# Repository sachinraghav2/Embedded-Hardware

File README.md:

# Embedded-Hardware
Contains eagle file while I developed the PCB of a multibot.

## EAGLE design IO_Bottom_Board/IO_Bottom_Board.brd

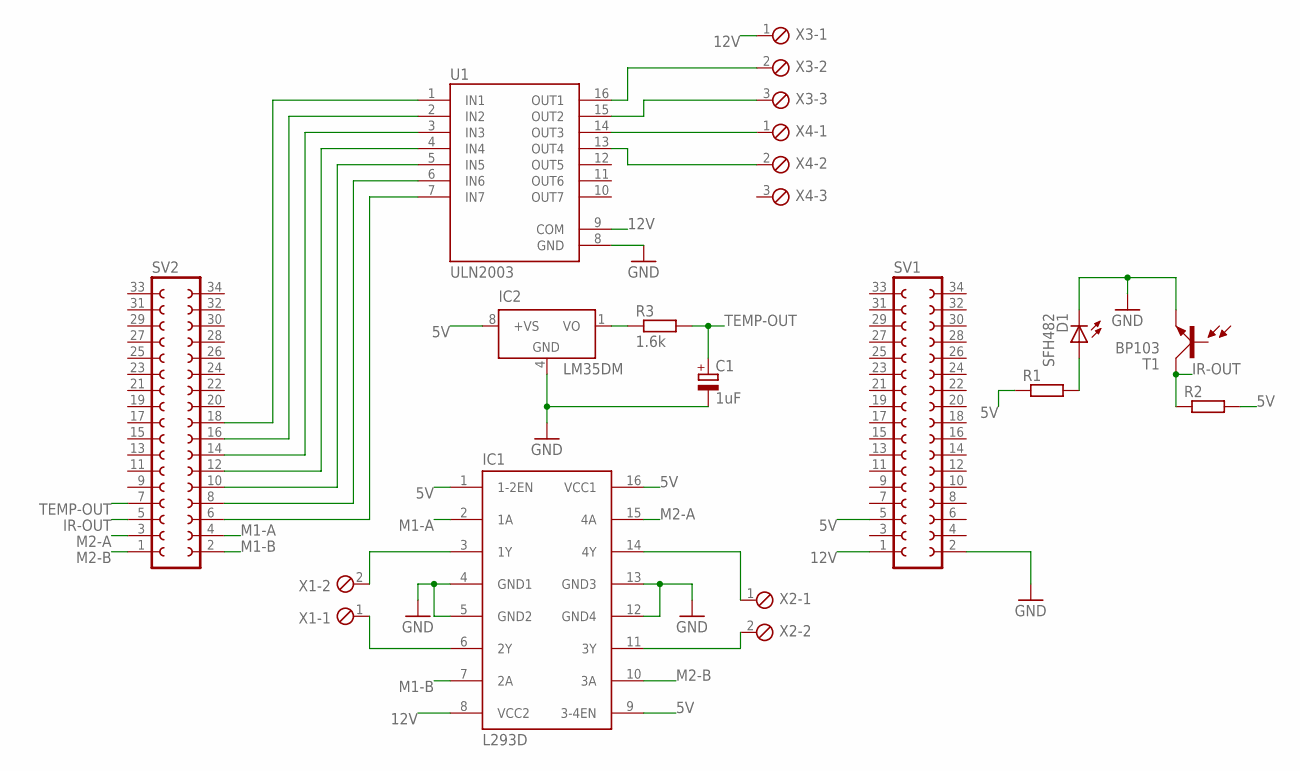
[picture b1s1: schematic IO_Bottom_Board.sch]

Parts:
C1: 1uF; CT3528
D1: SFH482
IC1: L293D; DIL16
IC2: LM35DM; SO08
R1, R2: R-EU_M2012; M2012
R3: 1.6k; M2012
SV1, SV2: FE17-2W
T1: BP103
U1: ULN2003; DIP762W46P254L1969H533Q16
X1, X2: MPT2; 2POL254
X3, X4: MPT3; 3POL254

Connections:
5V: IC1.1 (1-2EN), IC1.9 (3-4EN), IC1.16 (VCC1), IC2.8 (+VS), R1.1, R2.2, SV1.5
12V: IC1.8 (VCC2), SV1.1, U1.9 (COM), X3.1
GND: C1.-, D1.K (C), IC1.4 (GND1), IC1.5 (GND2), IC1.12 (GND4), IC1.13 (GND3), IC2.4 (GND), SV1.2, T1.E, U1.8 (GND)
IR-OUT: R2.1, SV2.5, T1.C
LM-OUT: IC2.1 (VO), R3.1
M1-A: IC1.2 (1A), SV2.4
M1-B: IC1.7 (2A), SV2.2
M2-A: IC1.15 (4A), SV2.3
M2-B: IC1.10 (3A), SV2.1
unnamed: IC1.3 (1Y), X1.2
unnamed: IC1.6 (2Y), X1.1
unnamed: IC1.14 (4Y), X2.1
unnamed: IC1.11 (3Y), X2.2
unnamed: SV2.6, U1.7 (IN7)
unnamed: SV2.8, U1.6 (IN6)
unnamed: SV2.10, U1.5 (IN5)
unnamed: SV2.12, U1.4 (IN4)
unnamed: SV2.14, U1.3 (IN3)
unnamed: SV2.16, U1.2 (IN2)
unnamed: SV2.18, U1.1 (IN1)
unnamed: U1.16 (OUT1), X3.2
unnamed: U1.15 (OUT2), X3.3
unnamed: U1.14 (OUT3), X4.1
unnamed: U1.13 (OUT4), X4.2
unnamed: D1.A, R1.2
TEMP-OUT: C1.+, R3.2, SV2.7

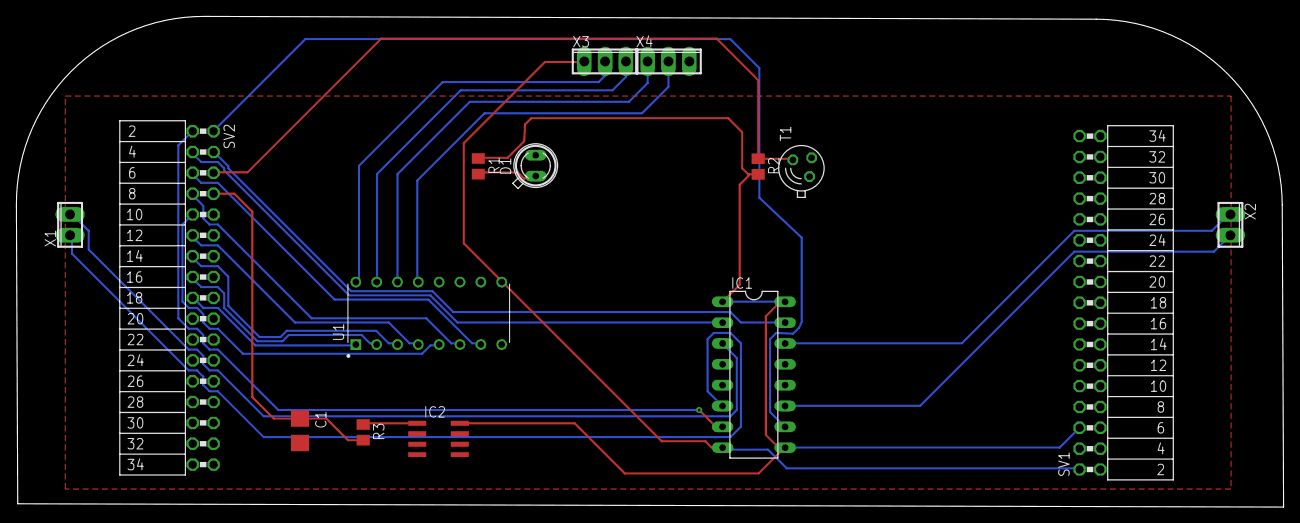
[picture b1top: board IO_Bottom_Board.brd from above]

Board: 2 copper layers, 154.5 x 59.8 mm, 15 parts (0 on the bottom side), 26 nets.

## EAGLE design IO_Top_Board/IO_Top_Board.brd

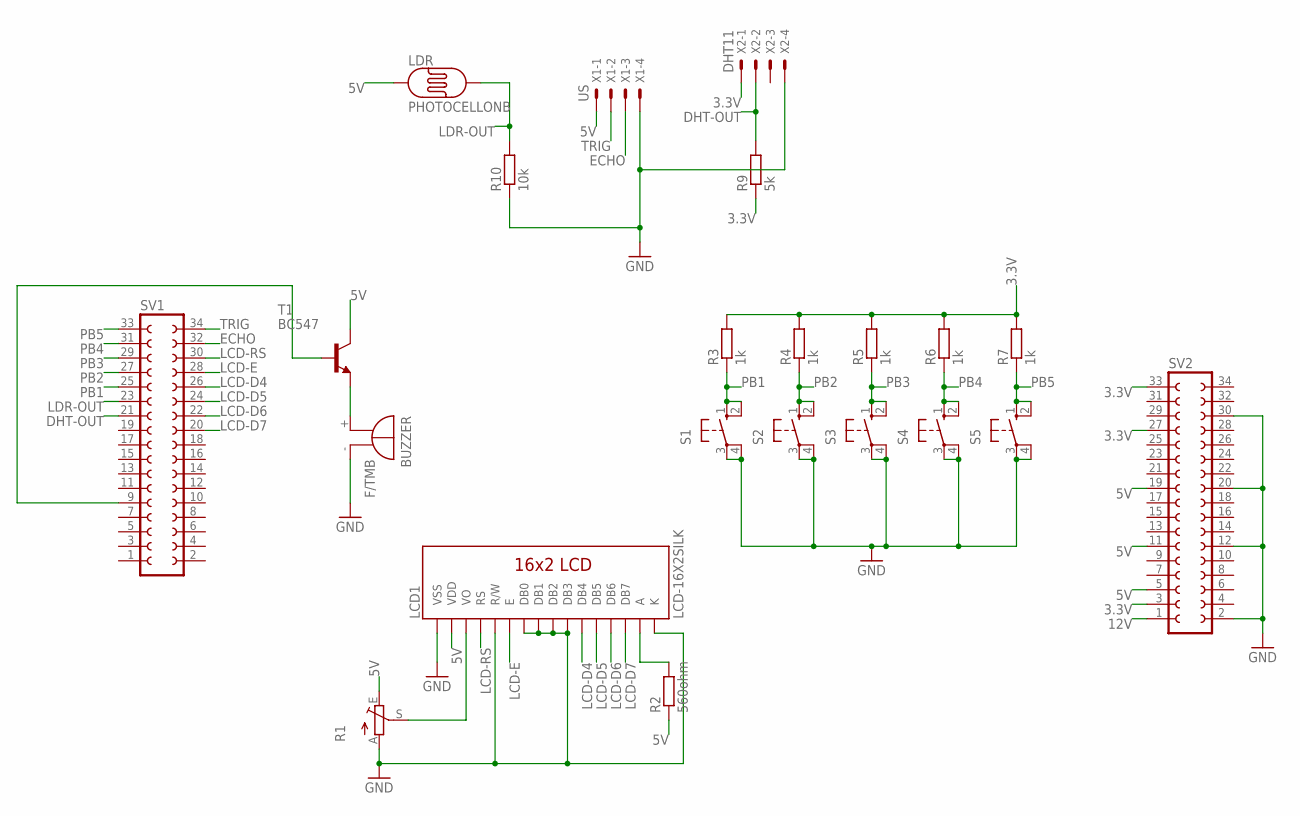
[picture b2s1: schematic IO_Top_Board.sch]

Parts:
BUZZER: F/TMB
LCD1: LCD-16X2SILK; LCD-16X2
LDR: PHOTOCELLONB; ON_BOARD
R1: TRIM_EU-CA6V; CA6V
R2: 560ohm; M0805
R3, R4, R5, R6, R7: 1k; M0805
R9: 5k; M0805
R10: 10k; M0805
S1, S2, S3, S4, S5: 10-XX; B3F-10XX
SV1, SV2: FE17-2W
T1: BC547; TO92
X1: US; 22-23-2041
X2: DHT11; 22-23-2041

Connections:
3.3V: R3.2, R4.2, R5.2, R6.2, R7.2, R9.1, SV2.3, SV2.27, SV2.33, X2.1
5V: LCD1.2 (VDD), LDR.1, R1.E, R2.1, SV2.5, SV2.11, SV2.19, T1.3 (C), X1.1
12V: SV2.1
DHT-OUT: R9.2, SV1.21, X2.2
ECHO: SV1.32, X1.3
GND: BUZZER.-, LCD1.1 (VSS), LCD1.5 (R/W), LCD1.7 (DB0), LCD1.8 (DB1), LCD1.9 (DB2), LCD1.10 (DB3), LCD1.16 (K), R1.A, R10.1, S1.3, S1.4 (P1), S2.3, S2.4 (P1), S3.3, S3.4 (P1), S4.3, S4.4 (P1), S5.3, S5.4 (P1), SV2.2, SV2.12, SV2.20, SV2.30, X1.4, X2.4
LCD-D4: LCD1.11 (DB4), SV1.26
LCD-D5: LCD1.12 (DB5), SV1.24
LCD-D6: LCD1.13 (DB6), SV1.22
LCD-D7: LCD1.14 (DB7), SV1.20
LCD-E: LCD1.6 (E), SV1.28
LCD-RS: LCD1.4 (RS), SV1.30
LDR-OUT: LDR.2, R10.2, SV1.23
unnamed: SV1.9, T1.2 (B)
unnamed: LCD1.3 (VO), R1.S
unnamed: BUZZER.+, T1.1 (E)
unnamed: LCD1.15 (A), R2.2
PB1: R3.1, S1.1 (S), S1.2 (S1), SV1.25
PB2: R4.1, S2.1 (S), S2.2 (S1), SV1.27
PB3: R5.1, S3.1 (S), S3.2 (S1), SV1.29
PB4: R6.1, S4.1 (S), S4.2 (S1), SV1.31
PB5: R7.1, S5.1 (S), S5.2 (S1), SV1.33
TRIG: SV1.34, X1.2

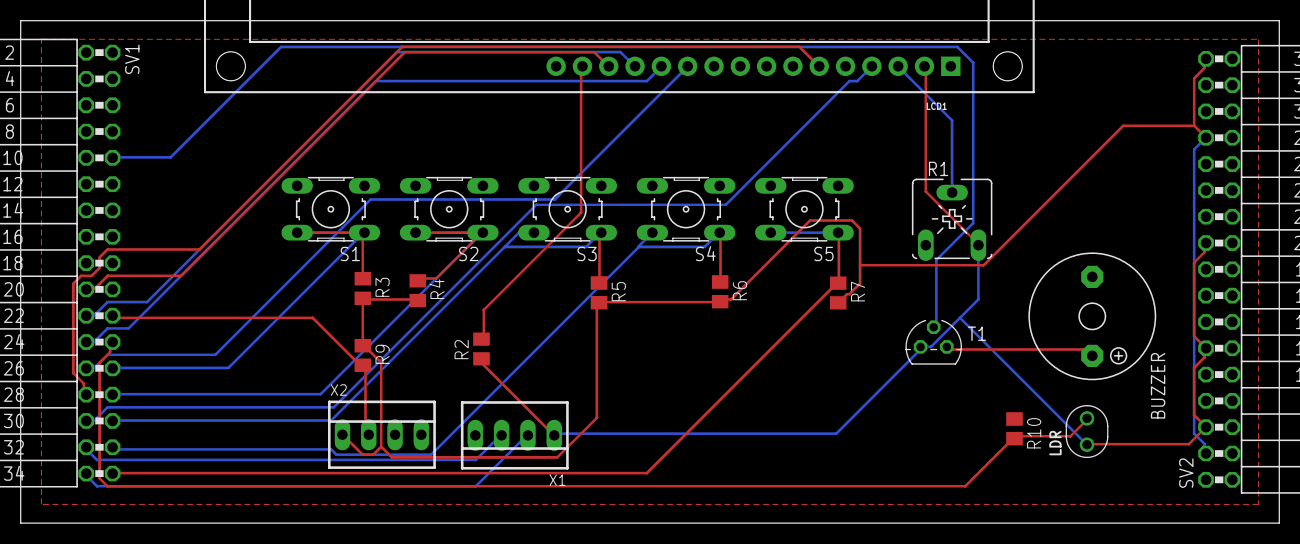
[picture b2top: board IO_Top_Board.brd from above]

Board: 2 copper layers, 121.5 x 48.5 mm, 22 parts (0 on the bottom side), 22 nets.

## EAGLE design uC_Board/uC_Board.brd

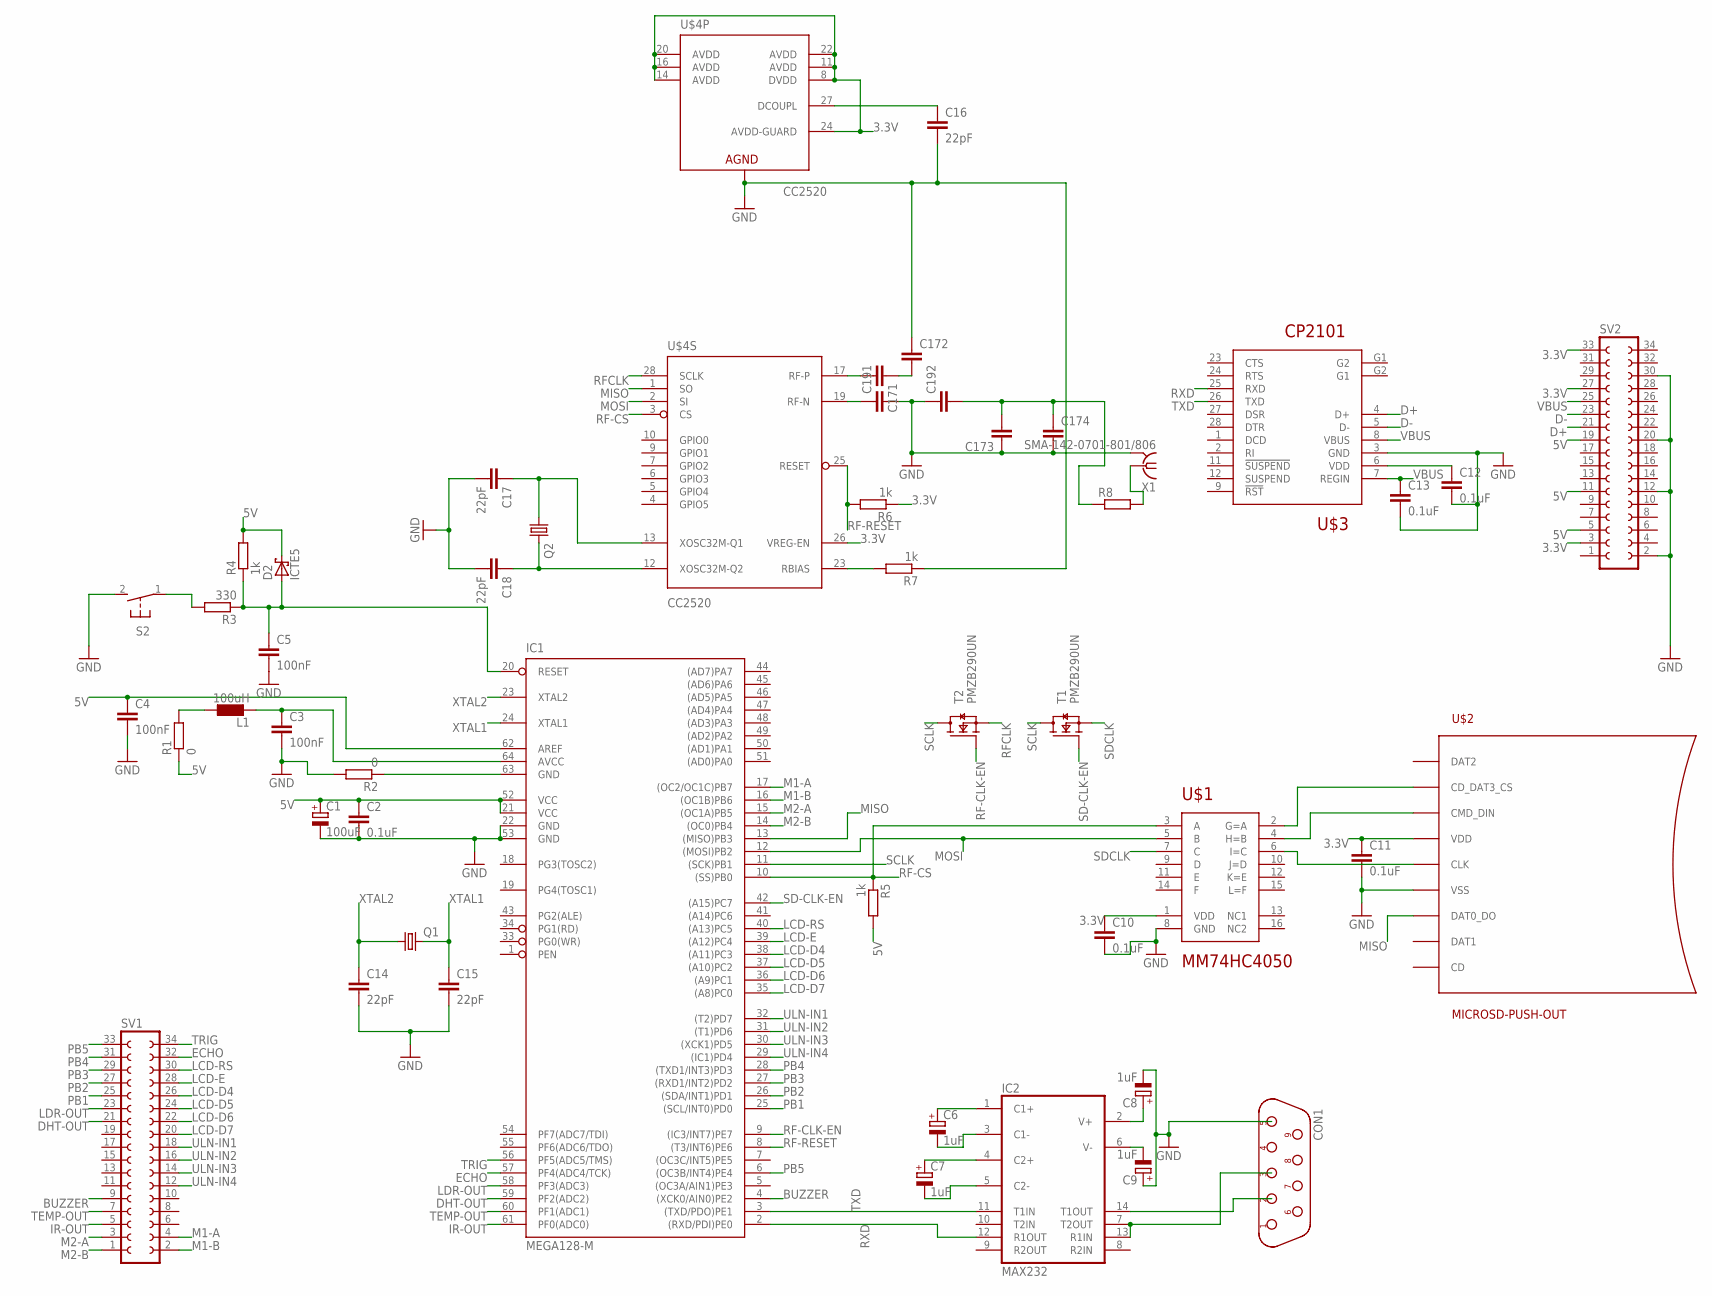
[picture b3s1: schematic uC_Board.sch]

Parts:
C1: 100uF; CT3528
C2, C10, C11, C12, C13: 0.1uF; C0805
C3, C4, C5: 100nF; C0805
C6, C7, C8, C9: 1uF; CT3528
C14, C15, C16, C17, C18: 22pF; C0805
C171, C172, C173, C174, C191, C192: C-EUC0201; C0201
CON1: DB9F; D-09F
D2: ICTE5; C4111-15
IC1: MEGA128-M; MLF64
IC2: MAX232; DIL16
L1: 100uH; 0207/10
Q1, Q2: CRYSTALCTS406; CTS406
R1, R2: 0; R0603
R3: 330; R0603
R4, R5, R6, R7: 1k; R0603
R8: R-EU_R0201; R0201
S2: 31-XX; B3F-31XX
SV1, SV2: FE17-2W
T1, T2: PMZB290UN; SOT883(B)
U$1: MM74HC4050
U$2: MICROSD-PUSH-OUT
U$3: CP2101
U$4: CC2520; QFN50P500X500X100-29N
X1: SMA-142-0701-801/806; J502-ND-142-0701-801/806

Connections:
3.3V: C10.1, C11.1, R6.1, SV2.3, SV2.27, SV2.33, U$1.1 (VDD), U$2.4 (VDD), U$4.8 (DVDD), U$4.11 (AVDD), U$4.14 (AVDD), U$4.16 (AVDD), U$4.20 (AVDD), U$4.22 (AVDD), U$4.24 (AVDD-GUARD), U$4.26 (VREG-EN)
5V: C1.+, C2.1, C4.1, D2.C, IC1.21 (VCC), IC1.52 (VCC), IC1.62 (AREF), L1.1, R1.1, R1.2, R4.2, R5.2, SV2.5, SV2.11, SV2.19
BUZZER: IC1.4 ((XCK0/AIN0)PE2), SV1.9
D+: SV2.21, U$3.4 (D+)
D-: SV2.23, U$3.5 (D-)
DHT-OUT: IC1.59 (PF2(ADC2)), SV1.21
ECHO: IC1.57 (PF4(ADC4/TCK)), SV1.32
GND: C1.-, C2.2, C3.2, C4.2, C5.2, C8.-, C9.+, C10.2, C11.2, C12.2, C13.2, C14.2, C15.2, C16.2, C17.2, C18.2, C172.1, C173.1, C174.2, C191.2, C192.1, CON1.5, IC1.22 (GND), IC1.53 (GND), IC2.15 (GND), R2.2, R7.1, S2.2 (S), SV2.2, SV2.12, SV2.20, SV2.30, U$1.8 (GND), U$2.6 (VSS), U$2.G1 (VSS), U$2.G2 (VSS), U$2.G3 (VSS), U$2.G4 (VSS), U$3.3 (GND), U$4.29 (AGND), X1.G@1 (2), X1.G@2 (2), X1.G@3 (2), X1.G@4 (2)
IR-OUT: IC1.61 (PF0(ADC0)), SV1.5
LCD-D4: IC1.38 ((A11)PC3), SV1.26
LCD-D5: IC1.37 ((A10)PC2), SV1.24
LCD-D6: IC1.36 ((A9)PC1), SV1.22
LCD-D7: IC1.35 ((A8)PC0), SV1.20
LCD-E: IC1.39 ((A12)PC4), SV1.28
LCD-RS: IC1.40 ((A13)PC5), SV1.30
LDR-OUT: IC1.58 (PF3(ADC3)), SV1.23
M1-A: IC1.17 ((OC2/OC1C)PB7), SV1.4
M1-B: IC1.16 ((OC1B)PB6), SV1.2
M2-A: IC1.15 ((OC1A)PB5), SV1.3
M2-B: IC1.14 ((OC0)PB4), SV1.1
MISO: IC1.13 ((MISO)PB3), U$2.7 (DAT0_DO), U$4.1 (SO)
MOSI: IC1.12 ((MOSI)PB2), U$1.5 (B), U$4.2 (SI)
unnamed: IC1.63 (GND), R2.1
unnamed: C3.1, IC1.64 (AVCC), L1.2
unnamed: U$1.2 (G=A), U$2.2 (CD_DAT3_CS)
unnamed: C5.1, D2.A, IC1.20 (RESET), R3.1, R4.1
unnamed: R3.2, S2.1
unnamed: C16.1, U$4.27 (DCOUPL)
unnamed: C6.+, IC2.1 (C1+)
unnamed: C6.-, IC2.3 (C1-)
unnamed: C7.+, IC2.4 (C2+)
unnamed: C7.-, IC2.5 (C2-)
unnamed: C9.-, IC2.6 (V-)
unnamed: C8.+, IC2.2 (V+)
unnamed: R7.2, U$4.23 (RBIAS)
unnamed: CON1.2, IC2.14 (T1OUT)
unnamed: CON1.3, IC2.7 (T2OUT), IC2.13 (R1IN)
unnamed: C171.2, U$4.17 (RF-P)
unnamed: C171.1, C172.2
unnamed: C191.1, U$4.19 (RF-N)
unnamed: U$1.4 (H=B), U$2.3 (CMD_DIN)
unnamed: U$1.6 (I=C), U$2.5 (CLK)
unnamed: C173.2, C174.1, C192.2, R8.1
unnamed: R8.2, X1.1
unnamed: C12.1, U$3.6 (VDD)
PB1: IC1.25 ((SCL/INT0)PD0), SV1.25
PB2: IC1.26 ((SDA/INT1)PD1), SV1.27
PB3: IC1.27 ((RXD1/INT2)PD2), SV1.29
PB4: IC1.28 ((TXD1/INT3)PD3), SV1.31
PB5: IC1.6 ((OC3B/INT4)PE4), SV1.33
RF-CLK-EN: IC1.9 ((IC3/INT7)PE7), T2.1 (G)
RF-CS: IC1.10 ((SS)PB0), R5.1, U$1.3 (A), U$4.3 (CS)
RF-RESET: IC1.8 ((T3/INT6)PE6), R6.2, U$4.25 (RESET)
RFCLK: T2.2 (S), U$4.28 (SCLK)
RXD: IC1.2 ((RXD/PDI)PE0), IC2.12 (R1OUT), U$3.25 (RXD)
SCLK: IC1.11 ((SCK)PB1), T1.3 (D), T2.3 (D)
SD-CLK-EN: IC1.42 ((A15)PC7), T1.1 (G)
SDCLK: T1.2 (S), U$1.7 (C)
TEMP-OUT: IC1.60 (PF1(ADC1)), SV1.7
TRIG: IC1.56 (PF5(ADC5/TMS)), SV1.34
TXD: IC1.3 ((TXD/PDO)PE1), IC2.11 (T1IN), U$3.26 (TXD)
ULN-IN1: IC1.32 ((T2)PD7), SV1.18
ULN-IN2: IC1.31 ((T1)PD6), SV1.16
ULN-IN3: IC1.30 ((XCK1)PD5), SV1.14
ULN-IN4: IC1.29 ((IC1)PD4), SV1.12
VBUS: C13.1, SV2.25, U$3.7 (REGIN), U$3.8 (VBUS)
VCC: IC2.16 (VCC)
XTAL1: C15.1, IC1.24 (XTAL1), Q1.3 (2)
XTAL2: C14.1, IC1.23 (XTAL2), Q1.1
XTAL3: C17.1, Q2.1, U$4.13 (XOSC32M-Q1)
XTAL4: C18.1, Q2.3 (2), U$4.12 (XOSC32M-Q2)

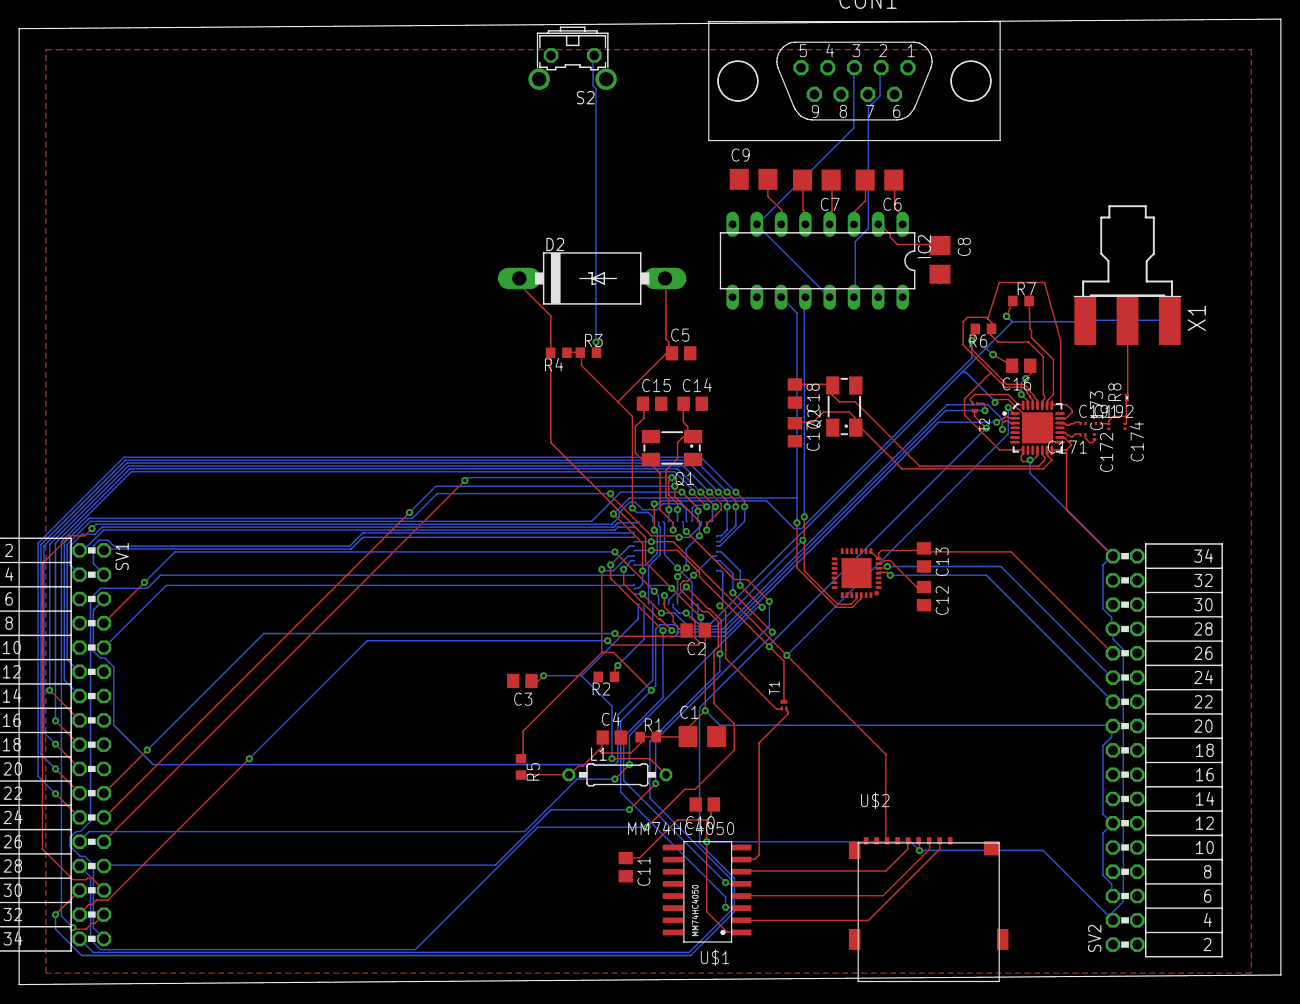
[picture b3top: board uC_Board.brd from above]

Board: 2 copper layers, 132.0 x 101.0 mm, 49 parts (1 on the bottom side), 70 nets.

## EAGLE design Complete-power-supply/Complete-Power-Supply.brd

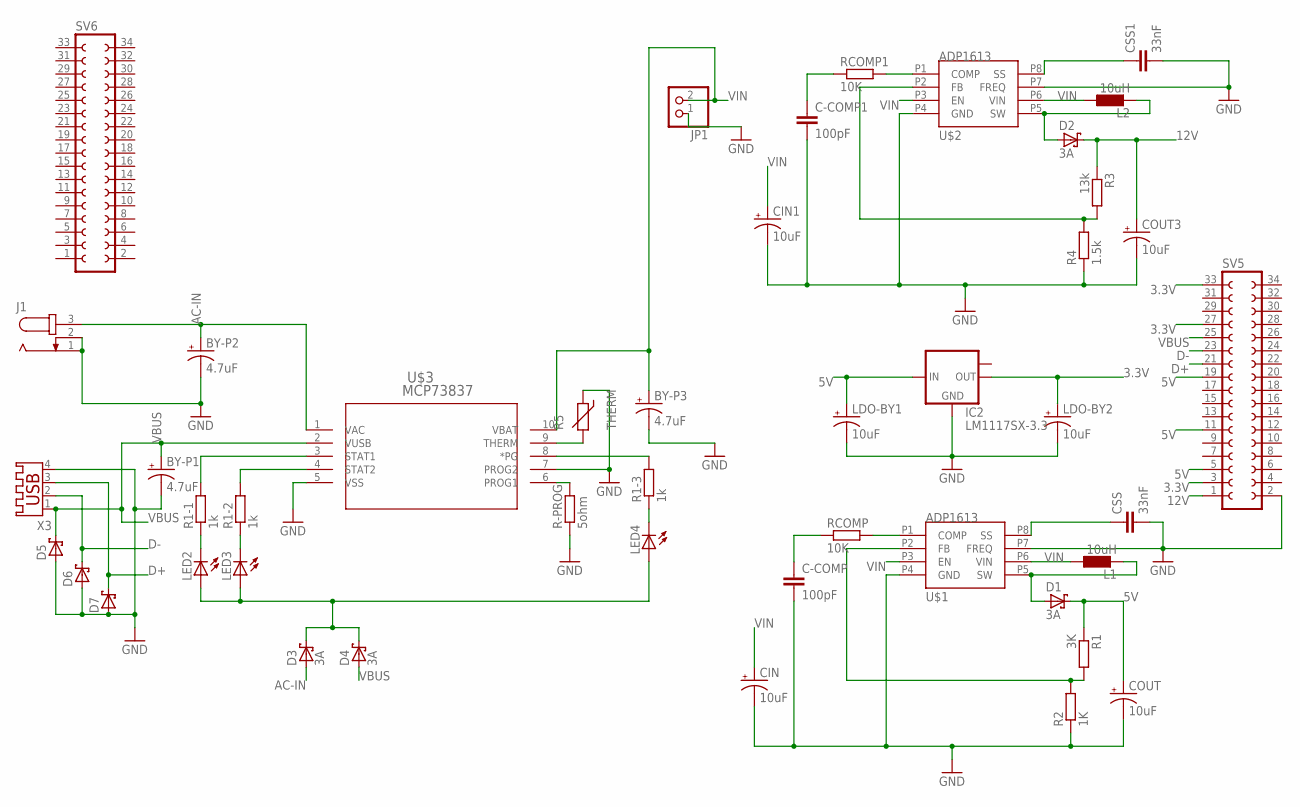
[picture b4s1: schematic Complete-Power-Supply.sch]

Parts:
BY-P1, BY-P2, BY-P3: 4.7uF; CT3528
C-COMP, C-COMP1: 100pF; C1206K
CIN, CIN1: 10uF; CT3528
COUT, COUT3: 10uF; CT3528
CSS, CSS1: 33nF; C1206K
D1, D2, D3, D4: 3A; SMB
D5, D6, D7: SCHOTTKY-DIODESMD; SMB
IC2: LM1117SX-3.3; TO263
J1: JACK-PLUG1; SPC4078
JP1: PINHD-1X2/90; 1X02/90
L1, L2: 10uH; 0207/10
LDO-BY1, LDO-BY2: 10uF; CT3528
LED2, LED3, LED4: LED_ESML0603; LED_SML0603
R1: 3K; M0805
R1-1, R1-2, R1-3: 1k; M0805
R2: 1K; M0805
R3: 13k; M0805
R4: 1.5k; M0805
R5: THERM; R-5
R-PROG: 5ohm; M0805
RCOMP, RCOMP1: 10K; M0805
SV5, SV6: FE17-2W
U$1, U$2: ADP1613; RM-8
U$3: MCP73837; SOP50P490X110-8N
X3: USB-A003

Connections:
3.3V: IC2.2 (OUT), LDO-BY2.- (+), SV5.3, SV5.27, SV5.33
5V: COUT.- (+), D1.C, IC2.3 (IN), LDO-BY1.- (+), R1.1, SV5.5, SV5.11, SV5.19
12V: COUT3.- (+), D2.C, R3.1, SV5.1
AC-IN: BY-P2.- (+), D3.A, J1.3, U$3.1 (VAC)
D+: D7.C, SV5.21, X3.3
D-: D6.C, SV5.23, X3.2
GND: BY-P1.+ (-), BY-P2.+ (-), BY-P3.+ (-), C-COMP.2, C-COMP1.2, CIN.+ (-), CIN1.+ (-), COUT.+ (-), COUT3.+ (-), CSS.2, CSS1.2, D5.A, D6.A, D7.A, IC2.1 (GND), J1.1, J1.2, JP1.1, LDO-BY1.+ (-), LDO-BY2.+ (-), R2.1, R4.1, R5.1, R-PROG.1, SV5.2, U$1.P4 (GND), U$1.P7 (FREQ), U$2.P4 (GND), U$2.P7 (FREQ), U$3.5 (VSS), U$3.7 (PROG2), X3.4
unnamed: CSS.1, U$1.P8 (SS)
unnamed: D1.A, L1.2, U$1.P5 (SW)
unnamed: RCOMP.2, U$1.P1 (COMP)
unnamed: C-COMP.1, RCOMP.1
unnamed: D2.A, L2.2, U$2.P5 (SW)
unnamed: R1.2, R2.2, U$1.P2 (FB)
unnamed: CSS1.1, U$2.P8 (SS)
unnamed: RCOMP1.2, U$2.P1 (COMP)
unnamed: R3.2, R4.2, U$2.P2 (FB)
unnamed: C-COMP1.1, RCOMP1.1
unnamed: R-PROG.2, U$3.6 (PROG1)
unnamed: R5.2, U$3.9 (THERM)
unnamed: LED2.C, R1-1.1
unnamed: R1-1.2, U$3.3 (STAT1)
unnamed: R1-2.2, U$3.4 (STAT2)
unnamed: R1-3.2, U$3.8 (*PG)
unnamed: LED3.C, R1-2.1
unnamed: LED4.C, R1-3.1
unnamed: D3.C, D4.C, LED2.A, LED3.A, LED4.A
VBUS: BY-P1.- (+), D4.A, D5.C, SV5.25, U$3.2 (VUSB), X3.1
VIN: BY-P3.- (+), CIN.- (+), CIN1.- (+), JP1.2, L1.1, L2.1, U$1.P3 (EN), U$1.P6 (VIN), U$2.P3 (EN), U$2.P6 (VIN), U$3.10 (VBAT)

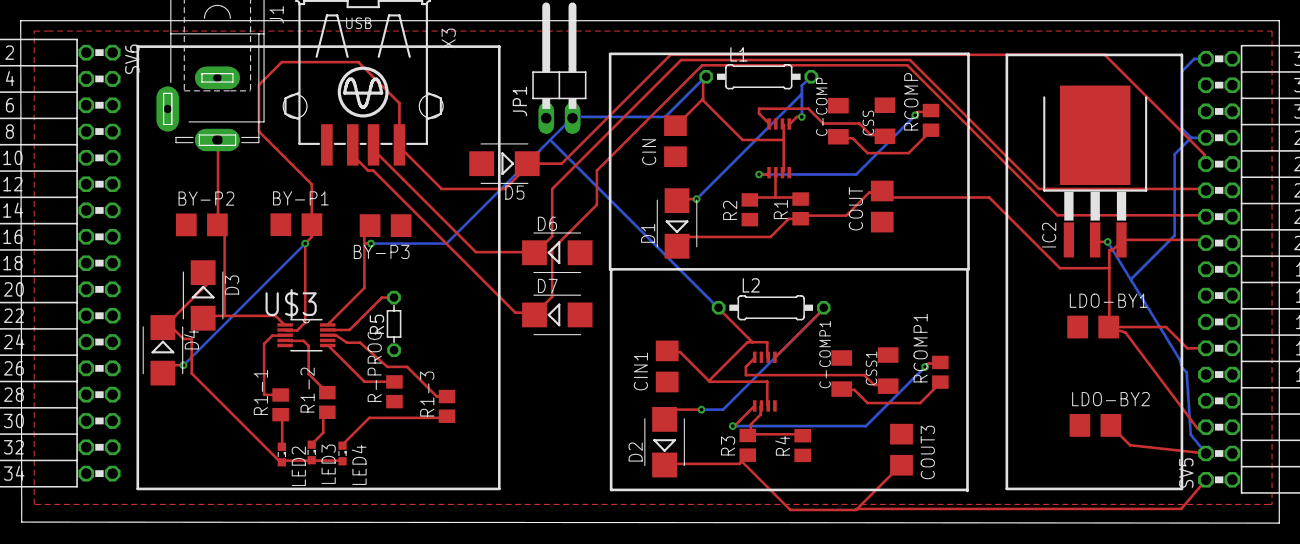
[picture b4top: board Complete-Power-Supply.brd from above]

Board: 2 copper layers, 121.5 x 48.5 mm, 45 parts (0 on the bottom side), 28 nets.

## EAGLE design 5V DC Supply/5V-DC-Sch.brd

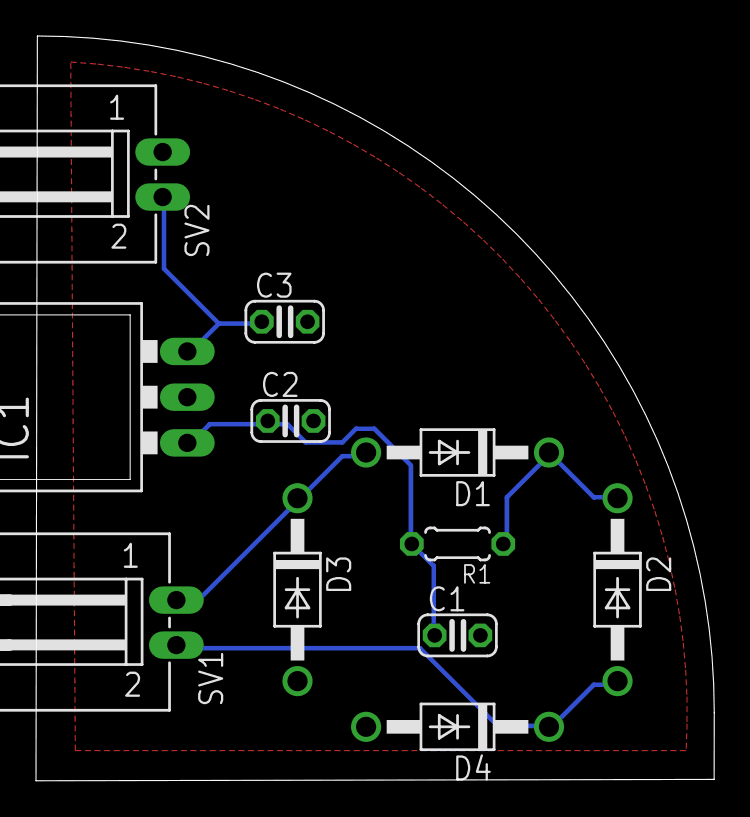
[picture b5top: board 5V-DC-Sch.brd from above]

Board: 2 copper layers, 37.7 x 41.4 mm, 11 parts (0 on the bottom side), 6 nets.

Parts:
C1, C2, C3: C025-024X044
D1, D2, D3, D4: 1N4004; DO41-10
IC1: 78XXL
R1: 0204/5
SV1, SV2: L02P

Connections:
GND: C1.2, C2.2, C3.2, D3.A, D4.A, IC1.GND, SV2.1
unnamed: D1.A, D3.C, SV1.1
unnamed: D1.C, D2.C, R1.1
unnamed: D2.A, D4.C, SV1.2
unnamed: C1.1, C2.1, IC1.IN, R1.2
unnamed: C3.1, IC1.OUT, SV2.2

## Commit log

2018-11-20 Update LICENSE

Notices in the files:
parts and their libraries:
SparkFun-Displays: Licensing: Creative Commons ShareAlike 4.0 International - https://creativecommons.org/licenses/by-sa/4.0
NXP_60_26022015: This library may be distributed and adapted freely for any purpose, as long as NXP is credited and any new creation is licensed under the same terms.
